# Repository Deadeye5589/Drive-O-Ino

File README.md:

# Drive-O-Ino
CAN Bus to Cartablet Converter Board with 60W USB-C PD

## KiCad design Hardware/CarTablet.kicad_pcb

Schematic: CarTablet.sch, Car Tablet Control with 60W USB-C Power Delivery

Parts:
C1, C10, C11, C12, C13, C15, C17, C18, C24, C25, C37, C38, C44, C45, C46, C53: 100nF; C_0805_2012Metric_Pad1.15x1.40mm_HandSolder
C2, C3: 100µF; C_1210_3225Metric_Pad1.42x2.65mm_HandSolder
C4, C5: 100nF; C_1206_3216Metric_Pad1.42x1.75mm_HandSolder
C6, C7: 10µF; C_1206_3216Metric_Pad1.42x1.75mm_HandSolder
C8: 39pF; C_0805_2012Metric_Pad1.15x1.40mm_HandSolder
C9: 820pF; C_0805_2012Metric_Pad1.15x1.40mm_HandSolder
C14, C41, C42: 4.7µF; C_0805_2012Metric_Pad1.15x1.40mm_HandSolder
C16, C54, C55: 4.7nF; C_0805_2012Metric_Pad1.15x1.40mm_HandSolder
C19, C21, C47: 10pF; C_0805_2012Metric_Pad1.15x1.40mm_HandSolder
C20, C23: 22pF; C_0805_2012Metric_Pad1.15x1.40mm_HandSolder
C22, C43, C52: 1µF; C_0805_2012Metric_Pad1.15x1.40mm_HandSolder
C26, C39, C40, C56, C57: 10nF; C_0805_2012Metric_Pad1.15x1.40mm_HandSolder
C27, C35: 100µF; CP_Elec_10x7.7
C28, C29, C30, C31, C32, C33, C34, C36: 10µF; C_0805_2012Metric_Pad1.15x1.40mm_HandSolder
C48: 1nF; C_0805_2012Metric_Pad1.15x1.40mm_HandSolder
C49: 1.5nF; C_0805_2012Metric_Pad1.15x1.40mm_HandSolder
C50, C51: 390pF; C_0805_2012Metric_Pad1.15x1.40mm_HandSolder
D1: B560C; D_SMC_Handsoldering
D2: SS36; D_SMC_Handsoldering
D3: P6SMB33CA; D_SMB_Handsoldering
D4: PESD1CAN; SOT-23; MPN PESD1CAN,215; Digi-Key_PN 1727-3817-1-ND
D5, D12, D13: 100V; D_SMB_Handsoldering
D6, D14, D15: 4.7V; D_SMB_Handsoldering
D7, D16, D17: BZX84B33; SOT-23
D8, D9: NSR0240H; D_SOD-323_HandSoldering
D10, D11: ESD7371; D_SOD-323_HandSoldering
FB1: 60 Ohm; L_1806_4516Metric_Pad1.57x1.80mm_HandSolder
H1, H2, H3, H4: MountingHole; MountingHole_3.2mm_M3_DIN965
IC1: TPS54540B-Q1; HSOP-8-1EP_3.9x4.9mm_P1.27mm_EP2.41x3.1mm
IC2: NCP81239; QFN-32-1EP_5x5mm_P0.5mm_EP3.6x3.6mm
IC3: EZ-PD_CCG2; QFN-24-1EP_4x4mm_P0.5mm_EP2.7x2.7mm
J1: ENABLE_KL15; PinHeader_1x02_P2.54mm_Vertical
J2: Anschluss; Molex_3482602124_SD
J3: I/O Expander; Molex_0901303208
J4: ISP; PinHeader_2x03_P2.54mm_Vertical
J8: Arduino; USB_Mini-B_Lumberg_2486_01_Horizontal
J11: PD_to_USB_Hub; USB_C_Receptacle_Amphenol_12401548E4-2A
J12: USB_Tablet_Input; USB_C_Receptacle_Amphenol_12401548E4-2A
J13: USB_Hub_Output; USB_C_Receptacle_Amphenol_12401548E4-2A
J14: JTAG; PinHeader_1x04_P2.54mm_Vertical
K1: IM23GR; Relay_DPDT_AXICOM_IMSeries_GullWing
L1: 3.3µH; L_10.4x10.4_H4.8
L2: CAN Drossel; ACT1210
L3: 4.2 uH; L_10.4x10.4_H4.8
Q1, Q2, Q3, Q4, Q5: NTTFS4C13NTAG; WDFN-8_3.3x3.3_Pitch0.65mm
Q6: FDG6335N; SOT-363_SC-70-6
R1: 365k; R_0805_2012Metric_Pad1.15x1.40mm_HandSolder
R2: 60k4; R_0805_2012Metric_Pad1.15x1.40mm_HandSolder
R3: 88k7; R_0805_2012Metric_Pad1.15x1.40mm_HandSolder
R4: 80k6; R_0805_2012Metric_Pad1.15x1.40mm_HandSolder
R5: 18k7; R_0805_2012Metric_Pad1.15x1.40mm_HandSolder
R6: 11k5; R_0805_2012Metric_Pad1.15x1.40mm_HandSolder
R7: JMP; R_0805_2012Metric_Pad1.15x1.40mm_HandSolder
R8, R14: nb; R_0805_2012Metric_Pad1.15x1.40mm_HandSolder
R9, R12: 61R9; R_0805_2012Metric_Pad1.15x1.40mm_HandSolder
R10, R11: 470; R_0805_2012Metric_Pad1.15x1.40mm_HandSolder
R13: 1M; R_0805_2012Metric_Pad1.15x1.40mm_HandSolder
R15, R17, R18, R21, R22, R27, R55, R56, R57, R58, R61, R63: 10k; R_0805_2012Metric_Pad1.15x1.40mm_HandSolder
R16, R19, R23, R59, R60: 1k; R_0805_2012Metric_Pad1.15x1.40mm_HandSolder
R20: 4k7; R_0805_2012Metric_Pad1.15x1.40mm_HandSolder
R24: 100; R_0805_2012Metric_Pad1.15x1.40mm_HandSolder
R25, R26: 5m; R_1206_3216Metric_Pad1.42x1.75mm_HandSolder
R28, R62, R64: 150; R_0805_2012Metric_Pad1.15x1.40mm_HandSolder
R29, R32: 4.02; R_0805_2012Metric_Pad1.15x1.40mm_HandSolder
R30, R31: 0; R_0805_2012Metric_Pad1.15x1.40mm_HandSolder
R33, R34, R35, R36, R38, R40: 10; R_0805_2012Metric_Pad1.15x1.40mm_HandSolder
R37: 1; R_0805_2012Metric_Pad1.15x1.40mm_HandSolder
R39: 90k9; R_0805_2012Metric_Pad1.15x1.40mm_HandSolder
R41: 20k; R_0805_2012Metric_Pad1.15x1.40mm_HandSolder
R42, R43: 20k5; R_0805_2012Metric_Pad1.15x1.40mm_HandSolder
R44: 24k3; R_0805_2012Metric_Pad1.15x1.40mm_HandSolder
R45, R48, R49: 2k2; R_0805_2012Metric_Pad1.15x1.40mm_HandSolder
R46: 19k1; R_0805_2012Metric_Pad1.15x1.40mm_HandSolder
R47: 4k75; R_0805_2012Metric_Pad1.15x1.40mm_HandSolder
R50: 499k; R_0805_2012Metric_Pad1.15x1.40mm_HandSolder
R51, R52, R53, R54: 0; R_0201_0603Metric
RV1, RV2: CT0603L25HSG; R_0603_1608Metric_Pad1.05x0.95mm_HandSolder
T1, T2, T3: MUN5313DW; SOT-363_SC-70-6_Handsoldering
U1: TJA1042T; SOIC-8_3.9x4.9mm_P1.27mm
U2: MCP2515-xSO; SOIC-18W_7.5x11.6mm_P1.27mm
U3: ATmega328P-AU; TQFP-32_7x7mm_P0.8mm
U4: FT232RL; SSOP-28_5.3x10.2mm_P0.65mm
Y1: 16 MHz; Crystal_SMD_3225-4Pin_3.2x2.5mm
Y2: 8 MHz; Crystal_SMD_3225-4Pin_3.2x2.5mm

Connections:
+5V: C2.1, C3.1, C10.1, C11.2, C12.1, C13.1, J4.2, L1.2, R2.1, R7.1, R10.1, R11.1, R15.1, R17.1, R51.2, U1.3 (VCC), U2.18 (VDD), U3.4 (VCC), U3.6 (VCC), U3.18 (AVCC)
+5VD: C42.1, C43.1, C44.1, C45.1, C46.1, IC2.30 (VCC), IC3.6 (VDD), IC3.8 (VDDIO), IC3.9 (VDD), R37.1, R45.1, R47.1, R48.1, R49.1
+12L: C27.1, C28.1, C29.1, C30.1, IC2.6 (V1), Q1.1 (S), R25.2, R35.2
+48V: C41.1, D8.2 (A), D9.2 (A), IC2.29 (VDRV), R37.2
/CS: U2.16 (~CS), U3.14 (PB2)
/EN_DCDC: IC2.16 (EN), IC3.15 (GPIO3)
/EXT_INPUT_1: R59.1, U3.24 (PC1)
/EXT_INPUT_2: R60.1, U3.25 (PC2)
/INT: U2.12 (~INT), U3.13 (PB1)
/INT_DCDC: IC2.11 (INT), IC3.14 (GPIO2), R45.2
/MISO: J4.1, U2.15 (SO), U3.16 (PB4)
/MOSI: J4.4, U2.14 (SI), U3.15 (PB3)
/Power_PD: R24.1, U3.1 (PD3)
/Remote12V: R27.1, T1.2 (B), U3.9 (PD5)
/Rx: R52.2, U3.30 (PD0)
/SCK: J4.3, U2.13 (SCK), U3.17 (PB5)
/STANDBY: U1.8 (STB), U3.12 (PB0)
/Tablet_PD: K1.1, U3.2 (PD4)
/Tx: R53.2, U3.31 (PD1)
/WAKE_INPUT: R19.1, U3.32 (PD2)
CAN_HIGH: D4.1 (C1), J2.7, L2.3, R8.2, R9.1, RV1.1
CAN_LOW: D4.2 (C2), J2.6, L2.1, R12.2, R14.2, RV2.2
IN_1: D12.1 (A1), J3.1, R55.1, R57.2
IN_2: D13.1 (A1), J3.2, R56.1, R58.2
KL15: J1.1, J2.5, R1.1
KL30: C5.1, D2.2 (A), D3.1 (A1), J1.2, J2.1, J2.2
KL31: C2.2, C3.2, C4.2, C6.2, C7.2, C8.2, C9.2, C10.2, C11.1, C12.2, C13.2, C14.2, C15.1, C16.2, C17.1, C18.2, C19.2, C20.2, C21.2, C22.1, C23.2, C24.2, C26.2, C27.2, C28.2, C29.2, C30.2, C31.2, C32.2, C33.2, C34.2, C35.2, C36.2, C41.2, C42.2, C43.2, C44.2, C45.2, C46.2, C47.2, C48.2, C49.2, C50.2, C51.2, C52.2, C53.2, C54.2, C55.2, C56.2, C57.2, D1.2 (A), D3.2 (A2), D4.3 (C3), D5.2 (A2), D6.2 (A), D10.2 (A), D11.2 (A), D12.2 (A2), D13.2 (A2), D14.2 (A), D15.2 (A), IC1.7 (GND), IC1.9, IC2.3 (PGND), IC2.7 (CS1), IC2.13 (AGND), IC2.14 (AGND), IC2.17 (PDRV), IC2.22 (PGND), IC2.33 (EP), IC3.25 (EP), J2.3, J2.4, J2.8, J3.5, J3.6, J3.7, J3.8, J4.6, J8.5 (GND), J8.6 (Shield), J11.A1 (GND), J11.A12 (GND), J11.B1 (GND), J11.B12 (GND), J11.S1 (SHIELD), J12.A1 (GND), J12.A12 (GND), J12.B1 (GND), J12.B12 (GND), J12.S1 (SHIELD), J13.A1 (GND), J13.A12 (GND), J13.B1 (GND), J13.B12 (GND), J13.S1 (SHIELD), J14.3, K1.8, Q4.1 (S), Q5.1 (S), R3.2, R4.2, R6.2, R21.2, R22.2, R23.2, R27.2, R28.2, R41.2, R42.2, R44.2, R50.2, R55.2, R56.2, R61.2, R62.2, R63.2, R64.2, RV1.2, RV2.1, U1.2 (GND), U2.9 (VSS), U3.3 (GND), U3.5 (GND), U3.21 (GND), U4.7 (GND), U4.18 (GND), U4.21 (GND), U4.25 (AGND), U4.26 (TEST)
unnamed: C1.1, D1.1 (K), IC1.8 (SW), L1.1
unnamed: C1.2, IC1.1 (BOOT)
unnamed: C4.1, C5.2
unnamed: C8.1, IC1.6 (COMP), R5.1
unnamed: C9.1, R5.2
unnamed: C14.1, C17.2, C18.1, R20.1, R51.1, U4.4 (VCCIO), U4.20 (VCC)
unnamed: C15.2, R7.2, U3.20 (AREF)
unnamed: C16.1, R9.2, R12.1
unnamed: C19.1, R13.1, U3.7 (XTAL1/PB6), Y1.1
unnamed: C20.1, U2.7 (OSC2), Y2.1
unnamed: C21.1, R13.2, U3.8 (XTAL2/PB7), Y1.3
unnamed: C22.2, U4.17 (3V3OUT)
unnamed: C23.1, U2.8 (OSC1), Y2.3
unnamed: C24.1, R15.2, R16.2
unnamed: C25.1, J4.5, R17.2, U3.29 (~RESET~/PC6)
unnamed: C25.2, R23.1, R54.2
unnamed: C26.1, D6.1 (K), R18.1, R19.2
unnamed: C31.1, C32.1, C33.1, C34.1, C35.1, FB1.1, R26.1, R36.1, R39.1
unnamed: C36.1, FB1.2, J11.A4 (VBUS), J11.A9 (VBUS), J11.B4 (VBUS), J11.B9 (VBUS)
unnamed: C37.1, IC2.31 (VSW1), L3.1, Q2.1 (S), Q4.3 (D)
unnamed: C37.2, D8.1 (K), IC2.32 (BST1)
unnamed: C38.1, D9.1 (K), IC2.25 (BST2)
unnamed: C38.2, IC2.26 (VSW2), L3.2, Q3.1 (S), Q5.3 (D)
unnamed: C39.1, IC2.4 (CSN1), R33.1
unnamed: C39.2, IC2.5 (CSP1), R35.1
unnamed: C40.1, IC2.21 (CSP2), R34.2
unnamed: C40.2, IC2.20 (CSN2), R36.2
unnamed: C47.1, IC2.15 (COMP), R43.1
unnamed: C48.1, IC2.18 (CS2), R44.1
unnamed: C49.1, R43.2
unnamed: C50.1, IC3.1 (CC2), J11.B5 (CC2)
unnamed: C51.1, IC3.2 (CC1), J11.A5 (CC1)
unnamed: C52.1, IC3.7 (VCCD)
unnamed: C53.1, IC3.16 (XRES), J14.4, R47.2
unnamed: C54.1, IC3.23 (GPIO8), IC3.24 (GPIO9), Q6.6 (D), R40.2, R50.1
unnamed: C55.1, IC3.17 (GPIO4), IC3.18 (GPIO5), Q6.3 (D), R38.2, R46.1
unnamed: C56.1, D14.1 (K), R57.1, R59.2
unnamed: C57.1, D15.1 (K), R58.1, R60.2
unnamed: D10.1 (K), J11.A7 (D-), J11.B7 (D-), R38.1
unnamed: D11.1 (K), J11.A6 (D+), J11.B6 (D+), R40.1
unnamed: IC1.3 (EN), R1.2, R3.1
unnamed: IC1.4 (RT/CLK), R4.1
unnamed: IC1.5 (FB), R2.2, R6.1
unnamed: IC2.1 (HSG1), R29.2
unnamed: IC2.2 (LSG1), R30.2
unnamed: IC2.9 (SDA), IC3.19 (I2C_SDA), R49.2
unnamed: IC2.10 (SCL), IC3.20 (I2C_SCL), R48.2
unnamed: IC2.19 (FB), R39.2, R41.1, R42.1
unnamed: IC2.23 (LSG2), R31.2
unnamed: IC2.24 (HSG2), R32.2
unnamed: IC3.11 (SWD_IO), J14.1
unnamed: IC3.12 (SWD_CLK), J14.2
unnamed: IC3.13 (GPIO1), R46.2
unnamed: IC3.22 (GPIO7), Q6.2 (G), Q6.5 (G)
unnamed: J8.2 (D-), U4.16 (USBD-)
unnamed: J8.3 (D+), U4.15 (USBD+)
unnamed: J12.A2 (TX1+), J13.A2 (TX1+)
unnamed: J12.A3 (TX1-), J13.A3 (TX1-)
unnamed: J12.A4 (VBUS), J12.A9 (VBUS), J12.B4 (VBUS), J12.B9 (VBUS), J13.A4 (VBUS), J13.A9 (VBUS), J13.B4 (VBUS), J13.B9 (VBUS)
unnamed: J12.A5 (CC1), K1.4
unnamed: J12.A6 (D+), J13.A6 (D+)
unnamed: J12.A7 (D-), J13.A7 (D-)
unnamed: J12.A8 (SBU1), J13.A8 (SBU1)
unnamed: J12.A10 (RX2-), J13.A10 (RX2-)
unnamed: J12.A11 (RX2+), J13.A11 (RX2+)
unnamed: J12.B2 (TX2+), J13.B2 (TX2+)
unnamed: J12.B3 (TX2-), J13.B3 (TX2-)
unnamed: J12.B5 (CC2), K1.5
unnamed: J12.B6 (D+), J13.B6 (D+)
unnamed: J12.B7 (D-), J13.B7 (D-)
unnamed: J12.B8 (SBU2), J13.B8 (SBU2)
unnamed: J12.B10 (RX1-), J13.B10 (RX1-)
unnamed: J12.B11 (RX1+), J13.B11 (RX1+)
unnamed: J13.A5 (CC1), K1.3
unnamed: J13.B5 (CC2), K1.6
unnamed: L2.2, R14.1, U1.6 (CANL)
unnamed: L2.4, R8.1, U1.7 (CANH)
unnamed: Q1.2 (G), R24.2
unnamed: Q2.2 (G), R29.1
unnamed: Q2.3 (D), R25.1, R33.2
unnamed: Q3.2 (G), R32.1
unnamed: Q3.3 (D), R26.2, R34.1
unnamed: Q4.2 (G), R30.1
unnamed: Q5.2 (G), R31.1
unnamed: Q6.1 (S), Q6.4 (S)
unnamed: R16.1, U2.17 (~RESET)
unnamed: R20.2, R22.1, U4.19 (~RESET~)
unnamed: R28.1, T1.1 (E)
unnamed: R52.1, U4.1 (TXD)
unnamed: R53.1, U4.5 (RXD)
unnamed: R54.1, U4.2 (DTR)
unnamed: R61.1, T2.2 (B), U3.26 (PC3)
unnamed: R62.1, T2.1 (E)
unnamed: R63.1, T3.2 (B), U3.27 (PC4)
unnamed: R64.1, T3.1 (E)
unnamed: T1.5 (B), T1.6 (C)
unnamed: T2.5 (B), T2.6 (C)
unnamed: T3.5 (B), T3.6 (C)
unnamed: U1.1 (TXD), U2.1 (TXCAN)
unnamed: U1.4 (RXD), U2.2 (RXCAN)
SWC1_RX: J2.11, R10.2, U3.19 (ADC6)
SWC2_RX: J2.12, R11.2, U3.22 (ADC7)
WAKE: D5.1 (A1), J2.9, R18.2, R21.1

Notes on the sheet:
VDRV
Rechtwinklig anordnen

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
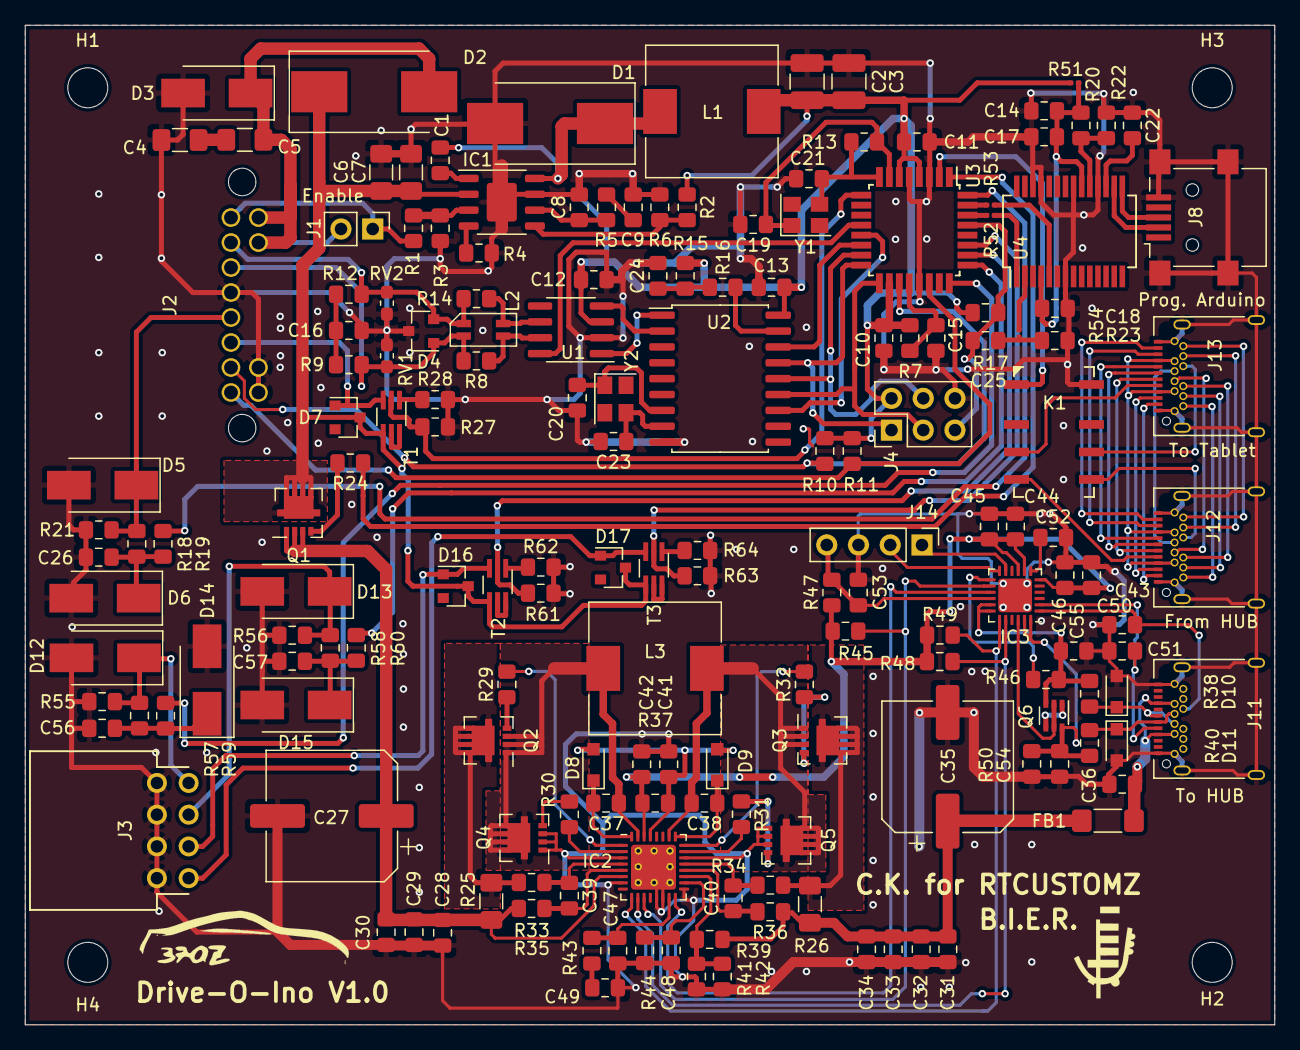
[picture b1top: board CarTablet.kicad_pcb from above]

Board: 2 copper layers, 100.0 x 80.0 mm, 176 parts (0 on the bottom side), 134 nets.

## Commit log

2020-05-04 V1.0 as ordered at JLCPCB
